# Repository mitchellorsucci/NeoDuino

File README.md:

# NeoDuino
Some random hardware project that initially started as a custom WS2812 / ATMEGA328 board

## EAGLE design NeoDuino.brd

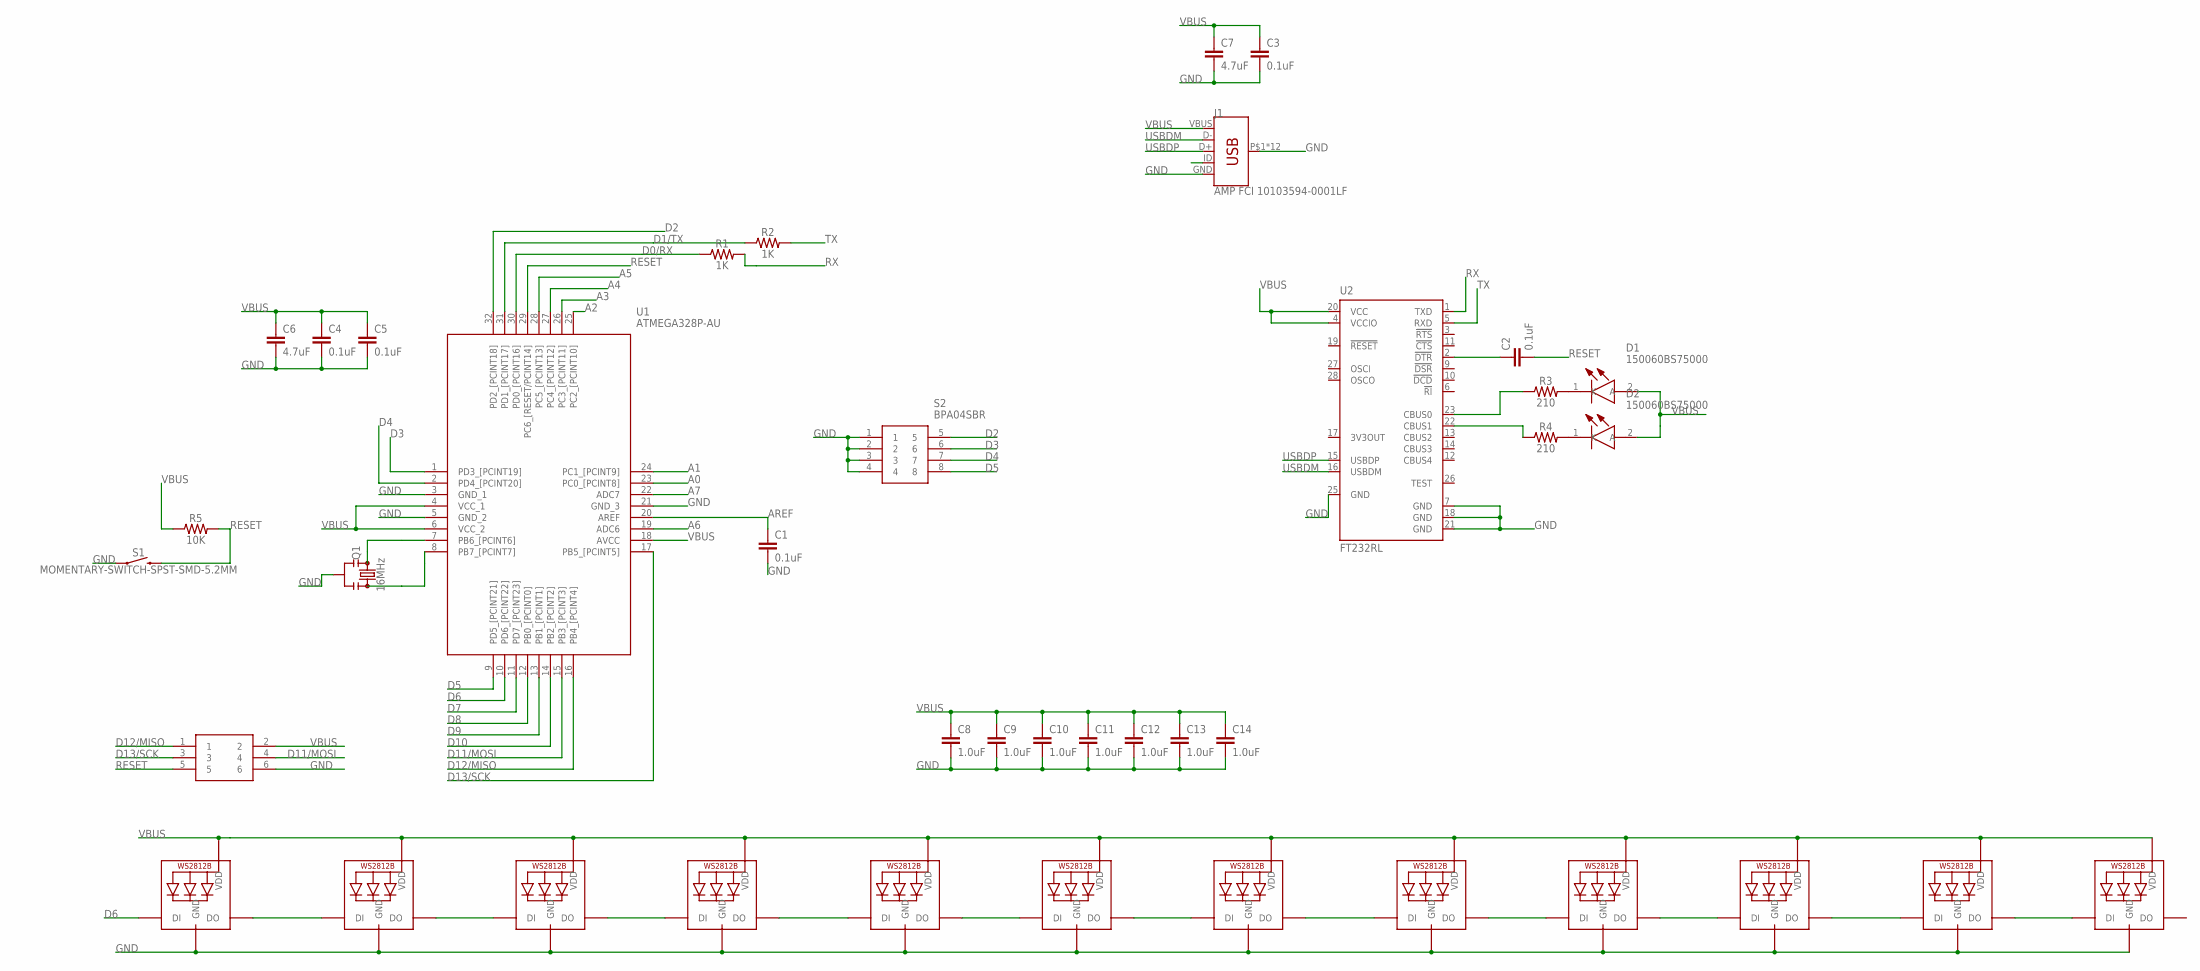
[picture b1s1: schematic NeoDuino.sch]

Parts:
C1, C2, C3, C4, C5: 0.1uF; 0402
C6, C7: 4.7uF; 0603
C8, C9, C10, C11, C12, C13, C14: 1.0uF; 0402
D1, D2: 150060BS75000; LEDC1608X80N
D3, D4, D5, D6, D7, D8, D9, D10, D11, D12, D13, D14: WS2812B5050; WS2812B
J1: AMP FCI 10103594-0001LF; USB-MICROB-PTH
J2: TSM-103-01-L-DH
Q1: 16MHz; RESONATOR-SMD-3.2X1.3
R1, R2: 1K; 0402
R3, R4: 210; 0402
R5: 10K; 0402
S1: MOMENTARY-SWITCH-SPST-SMD-5.2MM; TACTILE_SWITCH_SMD_5.2MM
S2: BPA04SBR
U1: ATMEGA328P-AU; QFP80P900X900X120-32N
U2: FT232RL; SSOP28

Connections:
A0: U1.23 (PC0_[PCINT8])
A1: U1.24 (PC1_[PCINT9])
A2: U1.25 (PC2_[PCINT10])
A3: U1.26 (PC3_[PCINT11])
A4: U1.27 (PC4_[PCINT12])
A5: U1.28 (PC5_[PCINT13])
A6: U1.19 (ADC6)
A7: U1.22 (ADC7)
AREF: C1.1, U1.20 (AREF)
D0/RX: R1.1, U1.30 (PD0_[PCINT16])
D1/TX: R2.1, U1.31 (PD1_[PCINT17])
D2: S2.5, U1.32 (PD2_[PCINT18])
D3: S2.6, U1.1 (PD3_[PCINT19])
D4: S2.7, U1.2 (PD4_[PCINT20])
D5: S2.8, U1.9 (PD5_[PCINT21])
D6: D3.4-DIN (DI), U1.10 (PD6_[PCINT22])
D7: U1.11 (PD7_[PCINT23])
D8: U1.12 (PB0_[PCINT0])
D9: U1.13 (PB1_[PCINT1])
D10: U1.14 (PB2_[PCINT2])
D11/MOSI: J2.4, U1.15 (PB3_[PCINT3])
D12/MISO: J2.1, U1.16 (PB4_[PCINT4])
D13/SCK: J2.3, U1.17 (PB5_[PCINT5])
GND: C1.2, C3.2, C4.2, C5.2, C6.2, C7.2, C8.2, C9.2, C10.2, C11.2, C12.2, C13.2, C14.2, D3.3-GND (GND), D4.3-GND (GND), D5.3-GND (GND), D6.3-GND (GND), D7.3-GND (GND), D8.3-GND (GND), D9.3-GND (GND), D10.3-GND (GND), D11.3-GND (GND), D12.3-GND (GND), D13.3-GND (GND), D14.3-GND (GND), J1.GND, J1.P$1 (SHIELD), J1.P$2 (SHIELD), J1.P$3 (SHIELD), J1.P$4 (SHIELD), J1.P$6 (SHIELD), J1.P$8 (SHIELD), J1.P$10 (SHIELD), J1.P$12 (SHIELD), J1.SHEILD2 (SHIELD), J1.SHIELD, J1.SHIELD3 (SHIELD), J1.SHIELD4 (SHIELD), J2.6, Q1.2, S1.1, S2.1, S2.2, S2.3, S2.4, U1.3 (GND_1), U1.5 (GND_2), U1.21 (GND_3), U2.7 (GND), U2.18 (GND), U2.21 (GND), U2.25 (GND)
unnamed: Q1.3, U1.8 (PB7_[PCINT7])
unnamed: C2.1, U2.2 (!DTR)
unnamed: R3.1, U2.23 (CBUS0)
unnamed: Q1.1, U1.7 (PB6_[PCINT6])
unnamed: D1.1 (K), R3.2
unnamed: D2.1 (K), R4.2
unnamed: R4.1, U2.22 (CBUS1)
unnamed: D5.2-DOUT (DO), D6.4-DIN (DI)
unnamed: D4.2-DOUT (DO), D5.4-DIN (DI)
unnamed: D3.2-DOUT (DO), D4.4-DIN (DI)
unnamed: D8.2-DOUT (DO), D9.4-DIN (DI)
unnamed: D11.2-DOUT (DO), D12.4-DIN (DI)
unnamed: D7.2-DOUT (DO), D8.4-DIN (DI)
unnamed: D6.2-DOUT (DO), D7.4-DIN (DI)
unnamed: D10.2-DOUT (DO), D11.4-DIN (DI)
unnamed: D9.2-DOUT (DO), D10.4-DIN (DI)
unnamed: D13.2-DOUT (DO), D14.4-DIN (DI)
unnamed: D12.2-DOUT (DO), D13.4-DIN (DI)
RESET: C2.2, J2.5, R5.2, S1.3 (2), U1.29 (PC6_[RESET/PCINT14])
RX: R1.2, U2.1 (TXD)
TX: R2.2, U2.5 (RXD)
USBDM: J1.D-, U2.16 (USBDM)
USBDP: J1.D+, U2.15 (USBDP)
VBUS: C3.1, C4.1, C5.1, C6.1, C7.1, C8.1, C9.1, C10.1, C11.1, C12.1, C13.1, C14.1, D1.2 (A), D2.2 (A), D3.1-VDD (VDD), D4.1-VDD (VDD), D5.1-VDD (VDD), D6.1-VDD (VDD), D7.1-VDD (VDD), D8.1-VDD (VDD), D9.1-VDD (VDD), D10.1-VDD (VDD), D11.1-VDD (VDD), D12.1-VDD (VDD), D13.1-VDD (VDD), D14.1-VDD (VDD), J1.VBUS, J2.2, R5.1, U1.4 (VCC_1), U1.6 (VCC_2), U1.18 (AVCC), U2.4 (VCCIO), U2.20 (VCC)

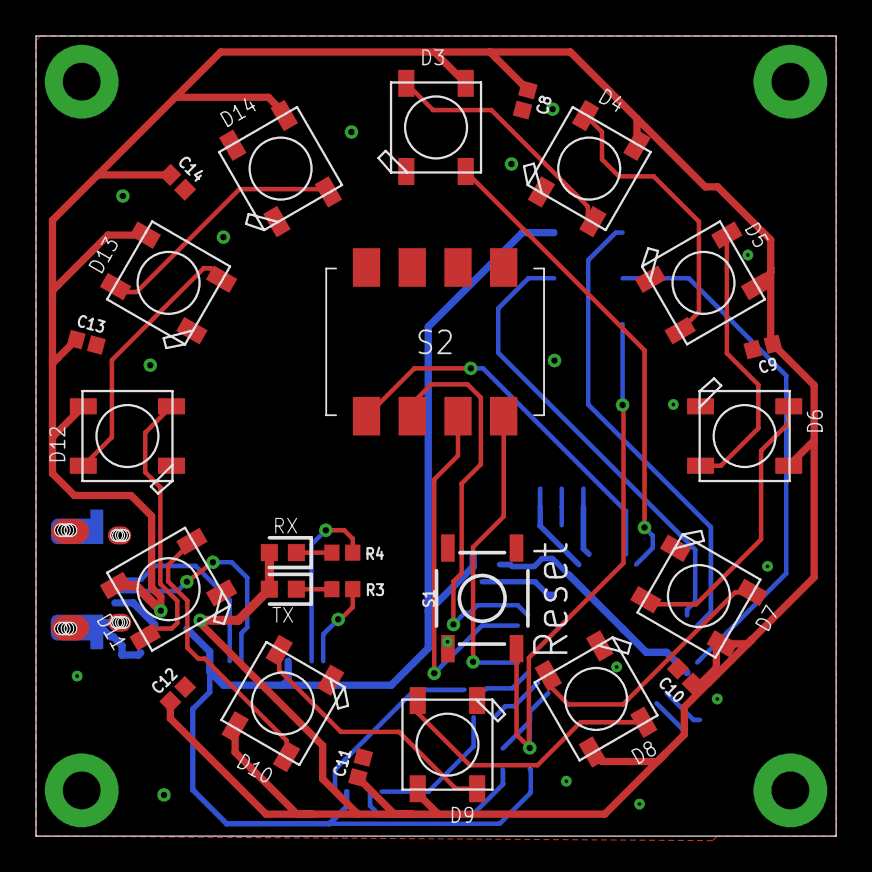
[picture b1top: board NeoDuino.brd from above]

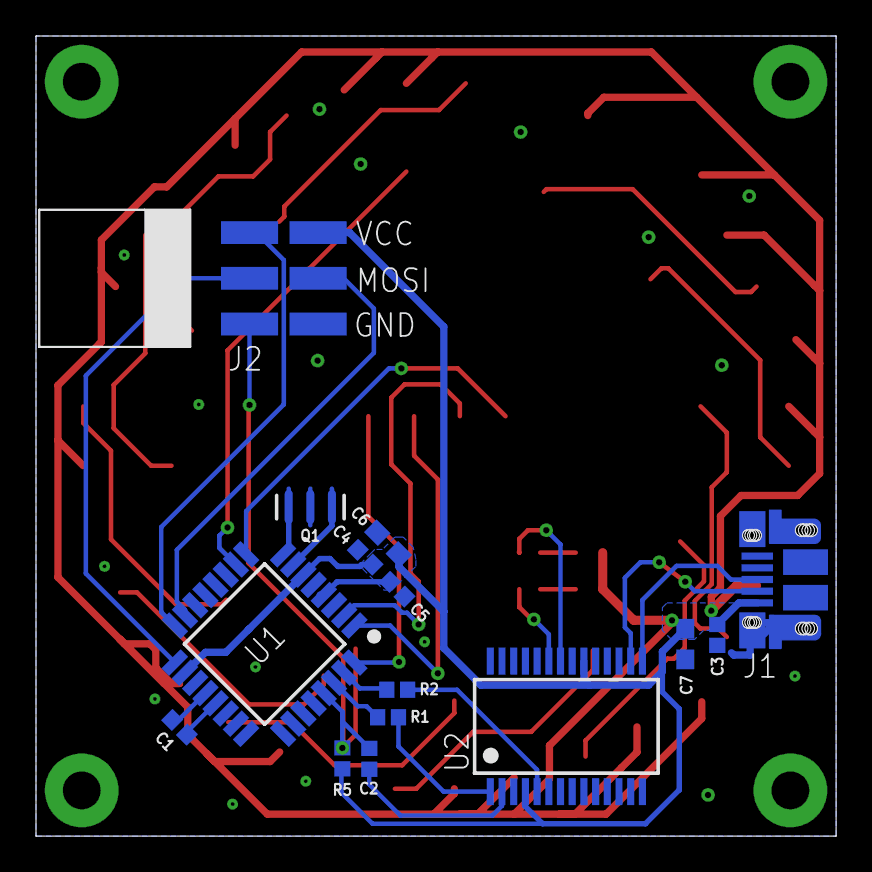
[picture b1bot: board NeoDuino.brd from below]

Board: 2 copper layers, 44.5 x 44.5 mm, 40 parts (15 on the bottom side), 36 nets.

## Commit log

2018-11-06 Added v0.5 pcb and schematic.

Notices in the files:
parts and their libraries:
SparkFun-Capacitors: Licensing: Creative Commons ShareAlike 4.0 International - https://creativecommons.org/licenses/by-sa/4.0
